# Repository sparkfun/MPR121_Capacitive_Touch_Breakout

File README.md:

**NOTE:** *This product has been retired from our catalog. If you are looking for more up-to-date info, please check out some of these resources to see how other users are still hacking and improving on this product.*
* *[SparkFun Forum](https://forum.sparkfun.com/)*
* *[Comments Here on GitHub](https://github.com/sparkfun/MPR121_Capacitive_Touch_Breakout/issues)*
* *[IRC Channel](https://www.sparkfun.com/news/263)*

MPR121 Capacitive Touch Sensor Breakout Board
=============================================

[  
*MPR121 Capacitive Touch Sensor Breakout Board (SEN-09695)*](https://www.sparkfun.com/products/9695)

This is a breakout  board for the MPR121QR2. It is a capacitive touch sensor controller driven by an I2C interface. The chip can control
up to twelve individual electrodes, as well as a simulated thirteenth electrode. 

Repository Contents
-------------------
* **/Firmware** - Example Arduino Sketch
* **/Hardware** - All Eagle design files (.brd, .sch)

License Information
-------------------
The hardware is released under [Creative Commons Share-alike 3.0](http://creativecommons.org/licenses/by-sa/3.0/).  
All other code is open source so please feel free to do anything you want with it; you buy me a beer if you use this and we meet someday ([Beerware license](http://en.wikipedia.org/wiki/Beerware)).

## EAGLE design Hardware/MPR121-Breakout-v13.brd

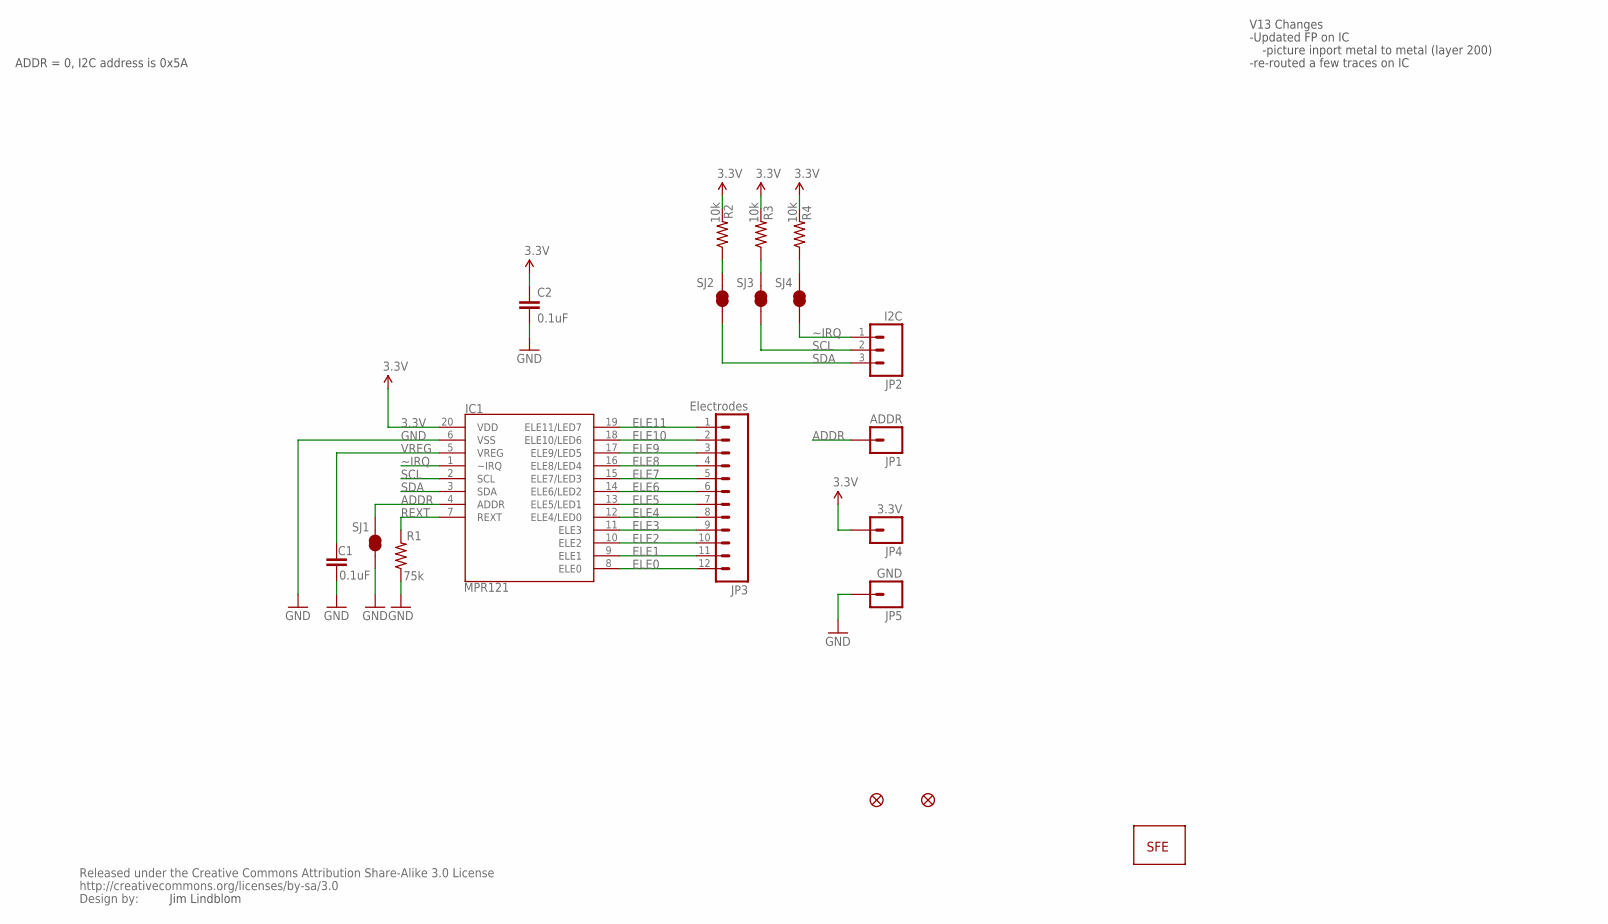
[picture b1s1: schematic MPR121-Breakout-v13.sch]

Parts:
C1, C2: 0.1uF; 0603-CAP
IC1: MPR121; QFN-20-0.4MM-V2
JP1: ADDR; 1X01
JP2: I2C; 1X03
JP3: Electrodes; 1X12
JP4: 3.3V; 1X01
JP5: GND; 1X01
JP7: LOGO-SFENEW; SFE-NEW-WEBLOGO
JP8, JP9: FIDUCIAL1X2; FIDUCIAL-1X2
R1: 75k; 0603-RES
R2, R3, R4: 10k; 0603-RES
SJ1, SJ2, SJ3, SJ4: SOLDERJUMPERTRACE; SJ_2S-TRACE
U$1: CREATIVE_COMMONS

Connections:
3.3V: C2.1, IC1.20 (VDD), JP4.1, R2.2, R3.2, R4.2
ADDR: IC1.4 (ADDR), JP1.1, SJ1.2
ELE0: IC1.8 (ELE0), JP3.12
ELE1: IC1.9 (ELE1), JP3.11
ELE2: IC1.10 (ELE2), JP3.10
ELE3: IC1.11 (ELE3), JP3.9
ELE4: IC1.12 (ELE4/LED0), JP3.8
ELE5: IC1.13 (ELE5/LED1), JP3.7
ELE6: IC1.14 (ELE6/LED2), JP3.6
ELE7: IC1.15 (ELE7/LED3), JP3.5
ELE8: IC1.16 (ELE8/LED4), JP3.4
ELE9: IC1.17 (ELE9/LED5), JP3.3
ELE10: IC1.18 (ELE10/LED6), JP3.2
ELE11: IC1.19 (ELE11/LED7), JP3.1
GND: C1.2, C2.2, IC1.6 (VSS), JP5.1, R1.1, SJ1.1
REXT: IC1.7 (REXT), R1.2
SCL: IC1.2 (SCL), JP2.2, SJ3.1
SCL_PU: R3.1, SJ3.2
SDA: IC1.3 (SDA), JP2.3, SJ2.1
SDA_PU: R2.1, SJ2.2
VREG: C1.1, IC1.5 (VREG)
~IRQ: IC1.1 (~IRQ), JP2.1, SJ4.1
~IRQ_PU: R4.1, SJ4.2

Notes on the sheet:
ADDR = 0, I2C address is 0x5A
Jim Lindblom
V13 Changes
-Updated FP on IC
-picture inport metal to metal (layer 200)
-re-routed a few traces on IC

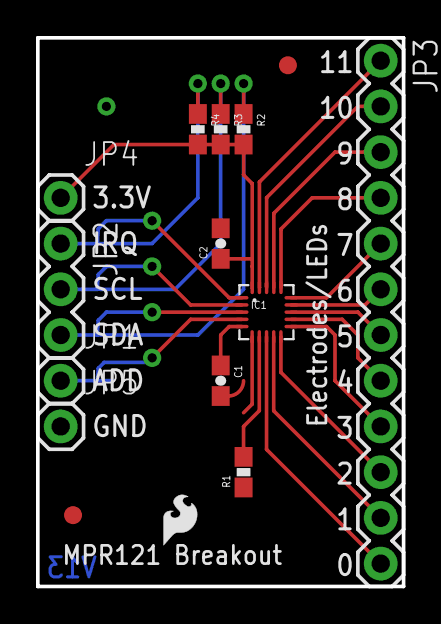
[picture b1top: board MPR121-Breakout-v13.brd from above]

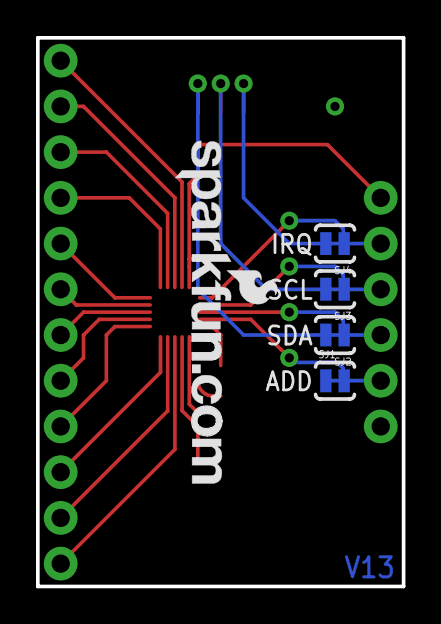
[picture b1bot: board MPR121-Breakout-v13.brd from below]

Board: 2 copper layers, 20.3 x 30.5 mm, 21 parts (5 on the bottom side), 23 nets.

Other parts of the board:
JP6: LOGO-SFESK; SFE-LOGO-FLAME

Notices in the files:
parts and their libraries:
SparkFun: Released under the Creative Commons Attribution Share-Alike 3.0 License
SparkFun-Aesthetics: Licensing: CC v3.0 Share-Alike You are welcome to use this library for commercial purposes.
